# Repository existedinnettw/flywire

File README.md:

# flywire

Point-to-point wiring for building a KiCad board by hand: wire wrap, fly wires on a
perfboard, or a carrier without copper. flywire reads the placed `.kicad_pcb`, joins every
net's through-hole pins with one wire per pair of pins, bends the wires so they keep off
other pads and off each other, and writes:

* `wiring.html`: one self-contained interactive page (no network needed, like
  [InteractiveHtmlBom](https://github.com/openscopeproject/InteractiveHtmlBom)): the board
  seen from the back with the wires as curves, and the wire list beside it;
* `wiring.txt`: the same wire list as text, with pin positions, lengths, cut lengths and
  the wires per pin (which to wrap first);
* `wiring.json`: the wiring, in the form the page exports and `--edits` reads back.

Copper tracks and zones are ignored; SMD pads are too (they do not reach the back).

**Demo:** [existedinnettw.github.io/flywire](https://existedinnettw.github.io/flywire/), the
page for [`examples/chaser`](examples/chaser) (a 555 clocking a CD4017 that walks four LEDs),
rebuilt by the `pages` workflow on every push to `main`
([wiring.txt](https://existedinnettw.github.io/flywire/wiring.txt),
[wiring.json](https://existedinnettw.github.io/flywire/wiring.json),
[chaser.kicad_pcb](https://existedinnettw.github.io/flywire/chaser.kicad_pcb)).

## use

```bash
uv tool install git+https://github.com/existedinnettw/flywire   # or: uvx --from ... flywire
flywire board.kicad_pcb                      # build/wiring.html, .txt, .json
flywire board.kicad_pcb --max-per-pin 3      # trees instead of chains
flywire board.kicad_pcb --edits wiring.json  # with what you changed on the page
```

| option | |
|---|---|
| `-o DIR`, `--name STEM` | where the files go (`build/wiring.*`) |
| `--max-per-pin N` | wires one pin may take. 2 (default): every net is the shortest chain through its pins; more: the shortest tree whose pins take at most N |
| `--slack MM` | added to every wire's cut length (10) |
| `--edits FILE` | a JSON export from the page: replaces the wires of every net it names, keeping its bends |
| `--straight` | do not bend the wires |

The exit status is 1 when the wiring has problems (a net in pieces, a pin over the limit);
they are listed at the end of `wiring.txt`.

## the page

* Wheel zooms, drag pans, double-click fits; **Back** / **Front** (`F`) flips the view (the
  back, where the wires are, is the default: x is mirrored).
* Click a wire or a row to select it, a pin to show its net; `↑` `↓` step through the list,
  `Space` ticks a wire done (kept in the browser, per board), **Hide done** hides them.
* **Edit** (`E`):
  * drag a wire's round handle to bend it;
  * drag a square end handle onto another pin of the same net to reconnect it;
  * click a pin, then another pin of its net, to add a wire;
  * `Del` deletes, `A` bends automatically, `S` straightens, `Ctrl+Z` undoes;
  * **Auto-bend** bends again every wire not bent by hand; **Reset** goes back to the proposal.
* The box above the list says when a net falls apart or a pin takes too many wires.
* **Export** downloads `wiring.json`; `flywire board.kicad_pcb --edits wiring.json` rebuilds
  the text list and the page with your changes, so they can be committed with the board.

## how the wires are bent

Each wire is a quadratic Bézier from pin to pin, given by the point half way along it. For
every wire a set of such midpoints, pushed sideways and along the chord, is priced: samples
of the curve inside a foreign pad's clearance, near another wire (a crossing costs little, a
wire lying along another a lot, except near a pin both end at), outside the board, and the
extra length. The longest wires go first, then every wire is placed again against all the
others until nothing changes. `src/flywire/bend.py` is the reference;
`src/flywire/web/bend.js` is the same algorithm for the page, and the tests check that the
two agree.

## develop

```bash
uv sync
uv run pytest        # needs node for the Python / JS bender comparison
uv run ruff format src tests && uv run ruff check src tests
uv run flywire examples/chaser/chaser.kicad_pcb    # the demo, in build/
```

`examples/chaser/chaser.kicad_pcb` is written by `examples/chaser/make_board.py` from
KiCad's stock footprints; it needs KiCad's `pcbnew` module, so run it with the Python KiCad
installs (`/usr/bin/python3 examples/chaser/make_board.py`).

The page is `src/flywire/web/` (`index.html`, `style.css`, `bend.js`, `app.js`), inlined
into one file with the board data by `report.html()`; it uses no libraries.

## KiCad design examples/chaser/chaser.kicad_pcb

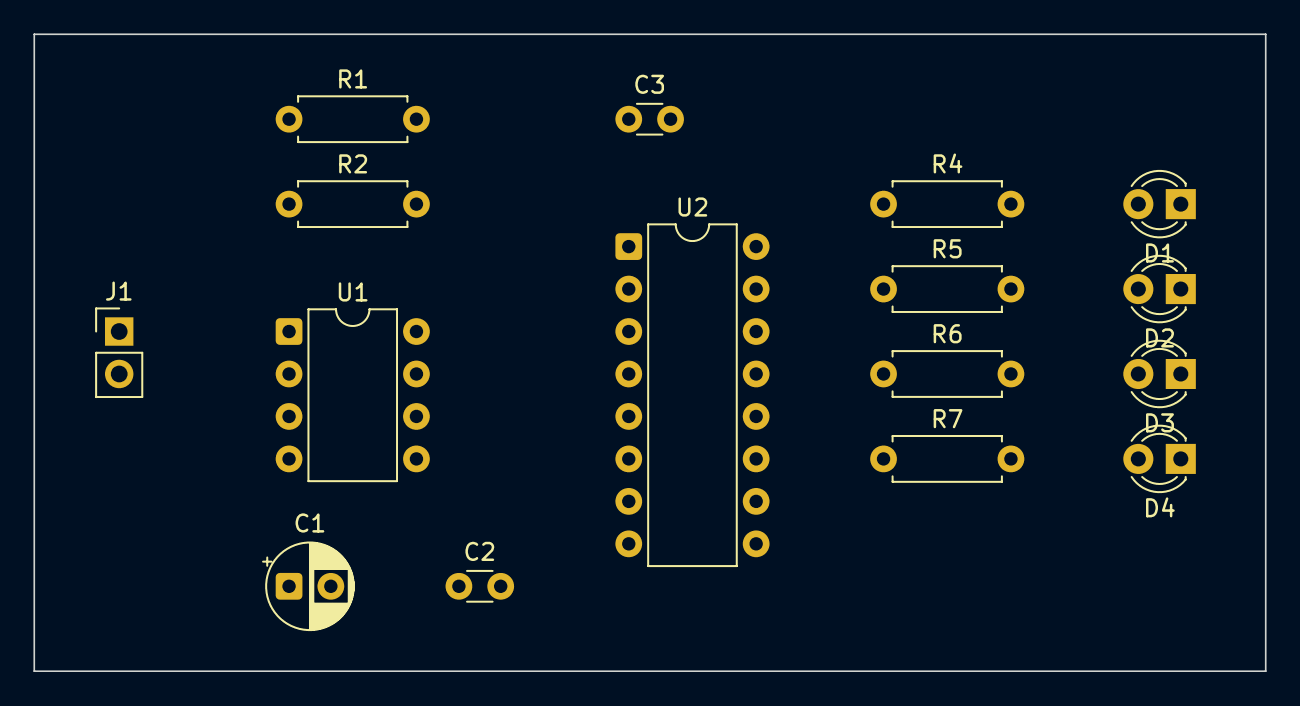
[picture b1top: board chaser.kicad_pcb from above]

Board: 2 copper layers, 73.7 x 38.1 mm, 16 parts (0 on the bottom side), 15 nets, no tracks yet.

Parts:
C1: 10u; CP_Radial_D5.0mm_P2.50mm
C2: 10n; C_Disc_D3.0mm_W1.6mm_P2.50mm
C3: 100n; C_Disc_D3.0mm_W1.6mm_P2.50mm
D1, D2, D3, D4: red; LED_D3.0mm
J1: 5V in; PinHeader_1x02_P2.54mm_Vertical
R1: 1k; R_Axial_DIN0207_L6.3mm_D2.5mm_P7.62mm_Horizontal
R2: 68k; R_Axial_DIN0207_L6.3mm_D2.5mm_P7.62mm_Horizontal
R4, R5, R6, R7: 470; R_Axial_DIN0207_L6.3mm_D2.5mm_P7.62mm_Horizontal
U1: NE555; DIP-8_W7.62mm
U2: CD4017; DIP-16_W7.62mm

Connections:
CLK: U1.3 (OUT), U2.14 (CLK)
CV: C2.1, U1.5 (CV)
DIS: R1.2, R2.1, U1.7 (DIS)
GND: C1.2 (-), C2.2, C3.2, D1.1 (K), D2.1 (K), D3.1 (K), D4.1 (K), J1.2 (GND), U1.1 (GND), U2.8 (VSS), U2.13 (/CE)
LED0: D1.2 (A), R4.2
LED1: D2.2 (A), R5.2
LED2: D3.2 (A), R6.2
LED3: D4.2 (A), R7.2
Q0: R4.1, U2.3 (Q0)
Q1: R5.1, U2.2 (Q1)
Q2: R6.1, U2.4 (Q2)
Q3: R7.1, U2.7 (Q3)
RST: U2.10 (Q4), U2.15 (RST)
THR: C1.1 (+), R2.2, U1.2 (TRIG), U1.6 (THR)
VCC: C3.1, J1.1 (+5V), R1.1, U1.4 (/RESET), U1.8 (VCC), U2.16 (VDD)
